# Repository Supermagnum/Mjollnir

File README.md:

# Mjollnir
A Bias-T cicuit board that handles 10A 60 volts DC.

Frequency range: 160 meters to 70 cm.

It has reverse polarity protection and protection from voltage spikes generated by relays.

The circuit boards are made so they actually are two boards, one injector and one extractor board.

They are easy to separate, as there are a line of closely spaced holes made for that exact purpose.

Voltage indicators should be LED with a proper non inductive current limiting resistor.

Schematic diagram and part numbers:

https://github.com/Supermagnum/Mjollnir/blob/main/10A-Bias-T-schem-BOM.pdf

Picture of the PCB :

https://github.com/Supermagnum/Mjollnir/blob/main/10A-Bias-T-front.jpg

PCB's:

https://aisler.net/p/ATXVEJSE

Bill of materials:

https://github.com/Supermagnum/Mjollnir/blob/main/bom.txt

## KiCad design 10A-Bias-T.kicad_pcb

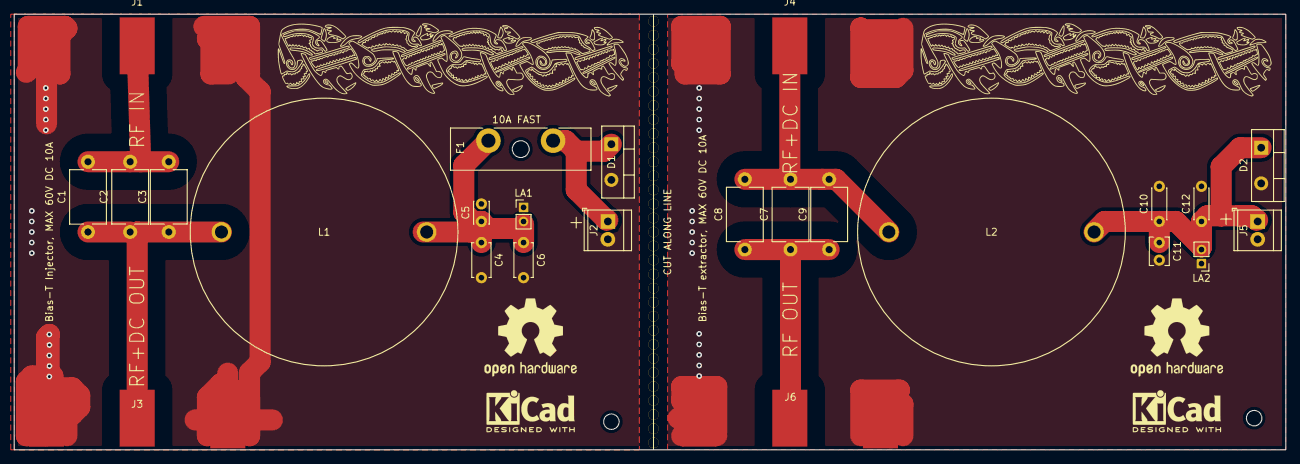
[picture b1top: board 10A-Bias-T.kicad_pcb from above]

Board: 2 copper layers, 181.0 x 62.0 mm, 25 parts (0 on the bottom side), 9 nets.

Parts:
C1, C2, C3, C7, C8, C9: 0.022µF; C_Disc_D7.5mm_W5.0mm_P10.00mm
C4: 1uF; C_Disc_D4.7mm_W2.5mm_P5.00mm
C5: 100uF; C_Disc_D3.0mm_W2.0mm_P2.50mm
C6: 0.1uF; C_Disc_D4.7mm_W2.5mm_P5.00mm
C10: 1uF; C_Disc_D4.3mm_W1.9mm_P5.00mm
C11: 100uF; C_Disc_D3.8mm_W2.6mm_P2.50mm
C12: 0.1uF; C_Disc_D4.3mm_W1.9mm_P5.00mm
D1, D2: D; TO-220-2_Vertical
F1: 10A; Fuseholder_Blade_ATO_Littelfuse_Pudenz_2_Pin
J1, J3, J4, J6: Conn_Coaxial; N
J2, J5: Conn_01x02_Female; TerminalBlock_TE_282834-2_1x02_P2.54mm_Horizontal
L1, L2: 1140-101K-RC; INDRD2921W163D3810H2616P
LA1, LA2: Lamp; PinHeader_1x02_P2.00mm_Vertical

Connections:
/DC+: C4.1, C5.1, C6.1, F1.1, L1.2, LA1.2
/DC+2: C10.1, C11.1, C12.1, D2.1, J5.1, L2.2, LA2.2
/RF: C1.2, C2.2, C3.2, J1.1
/RF2: C7.1, C8.1, C9.1, J6.1
/RF+DC: C1.1, C2.1, C3.1, J3.1, L1.1
/RF+DC2: C7.2, C8.2, C9.2, J4.1, L2.1
Earth: C4.2, C5.2, C6.2, D1.2, J1.2, J1.3, J2.2, J3.2, J3.3, LA1.1
GND: C10.2, C11.2, C12.2, D2.2, J4.2, J4.3, J5.2, J6.2, J6.3, LA2.1
unnamed: D1.1, F1.2, J2.1

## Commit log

2020-10-07 Add files via upload
    Added gerber files
2020-10-07 Add files via upload
    added misc files.
2020-10-07 added bom.
2020-10-07 Add files via upload
    added BOMS
2020-10-11 Add files via upload
    updates
2020-10-11 Add files via upload
    Updates, removed unnecessary components.
2020-12-20 Add files via upload
    updated gerbers
2020-12-20 Add files via upload
    updated pictures
2020-12-20 Add files via upload
    updated
